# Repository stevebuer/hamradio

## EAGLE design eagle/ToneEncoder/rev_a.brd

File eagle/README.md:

# Eagle CAD Projects

Two tone encoder boards for older 2 Meter radios, that have a tone switch but require an optional board.

## Prototypes

These were made by [Osh Park](https://oshpark.com).

* [Simple Tone Encoder](SimpleEncoder)

* [Tone Encoder](ToneEncoder)

## Assembly and Testing

* Todo

## Conversion to KiCad

* Todo

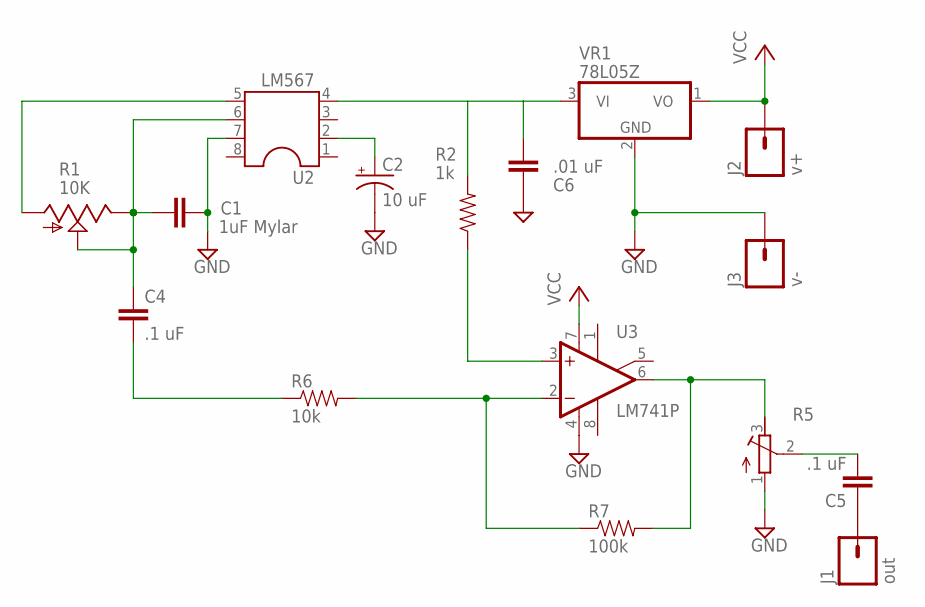
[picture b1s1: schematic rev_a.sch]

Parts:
C1: 1uF Mylar; C5B2.5
C2: 10 uF; CPOL-RADIAL-10UF-25V
C4: .1 uF; C2.5-2
C5: .1 uF; CAP-PTH-SMALL2
C6: .01 uF; C2.5-2
J1: out; 1X01_OFFSET
J2: v+; 1X01_OFFSET
J3: v-; 1X01_OFFSET
R1: 10K; S64W
R2: 1k; AXIAL-0.1
R5: RTRIM-3362P; RTRIM3362P
R6: 10k; AXIAL-0.1
R7: 100k; AXIAL-0.1
U2: LM567; DIL08
U3: LM741P; DIL08
VR1: 78L05Z; TO92

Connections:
GND: C2.2 (-), C6.2, J3.1, R5.1, U3.4 (V-), VR1.2 (GND)
unnamed: C6.1, U2.4, VR1.3 (VI)
unnamed: R2.P$1 (1), U3.3 (+IN)
unnamed: R6.P$2 (2), R7.P$1 (1), U3.2 (-IN)
unnamed: R5.3, R7.P$2 (2), U3.6 (OUT)
unnamed: C5.2, R5.2
unnamed: C4.2, R6.P$1 (1)
unnamed: C2.1 (+), U2.2
unnamed: C1.1, C4.1, R1.E, R1.S, U2.6
unnamed: C1.2, U2.7
unnamed: R1.A, U2.5
unnamed: C5.1, J1.1
VCC: J2.1, U3.7 (V+), VR1.1 (VO)

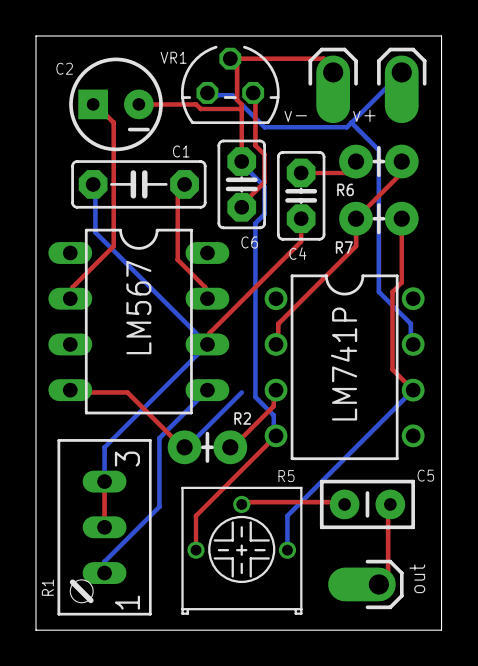
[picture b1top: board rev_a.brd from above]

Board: 2 copper layers, 22.5 x 33.0 mm, 16 parts (0 on the bottom side), 13 nets.

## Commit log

2022-03-27 add axports
2022-03-27 add uhf port frequency
2022-03-27 radio and signalink settings
2022-03-27 direwolf config and Makefile
2022-11-28 add grid program, move aprs files here
2022-12-02 Add script for windows location service
2022-12-02 set executable
2022-12-02 APRS telemetry script
2023-07-31 Add weather script
2023-08-01 telemetry random walk
2023-11-27 Change test case to Poulbo
2025-04-02 add dpkg files for tracker
2025-04-02 add hf 300 baud config
2025-04-03 add initial java library
2025-04-03 add ant build.xml
2025-04-05 update direwolf tracker config
2025-04-07 add bluetooth.md for serial port connection
2025-04-07 add bluetooth serial
2025-04-07 fix FX25 config line error
2025-07-09 import cs143 final project
2025-09-24 Create mfj-1699.md
    Initial version
2025-09-24 Update mfj-1699.md
    Add some measured lengths
2025-10-07 Update mfj-1699.md
    add 15m
2025-10-08 add weather tracker
2025-12-20 add android auto outline
2025-12-20 re-org tracker
2025-12-20 revamp tracker
2025-12-20 add gps share, map view, band set
2025-12-21 separate out beacon server
2025-12-21 create tracker package
2025-12-21 fixed build issues
2025-12-22 debugging fixes, make gps and iot config options
2025-12-22 add testing mode
2025-12-23 consolidate REST on same port, create openapi.yaml
2025-12-23 rename test-gps to test-api and expand api testing
2025-12-23 debug connection issues. split screens out.
2025-12-23 remove usb serial, band change once on connect
2025-12-23 move to SSE for sockets, FastAPI for REST
2025-12-23 fixed osm bugs., add button to clear decodes
2025-12-24 android auto debugging
2025-12-24 rewrite auto app for messaging api
2026-03-06 add tone encoder boards
2026-03-06 add PCB images

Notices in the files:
parts and their libraries:
SparkFun-Capacitors: Licensing: Creative Commons ShareAlike 4.0 International - https://creativecommons.org/licenses/by-sa/4.0
